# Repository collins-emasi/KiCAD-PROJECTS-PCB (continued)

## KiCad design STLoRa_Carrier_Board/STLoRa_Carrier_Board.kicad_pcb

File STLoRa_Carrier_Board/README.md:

# STLoRa Carrier Board
This is a carrier board for the M.2 Key B System on Module board I designed.

Some of the features include
- SWD Debugging
- UART, I2C peripherals
- Battery powered
- M.2 Key B connector

# Images

# KiCAD
I am using KiCAD v7.0

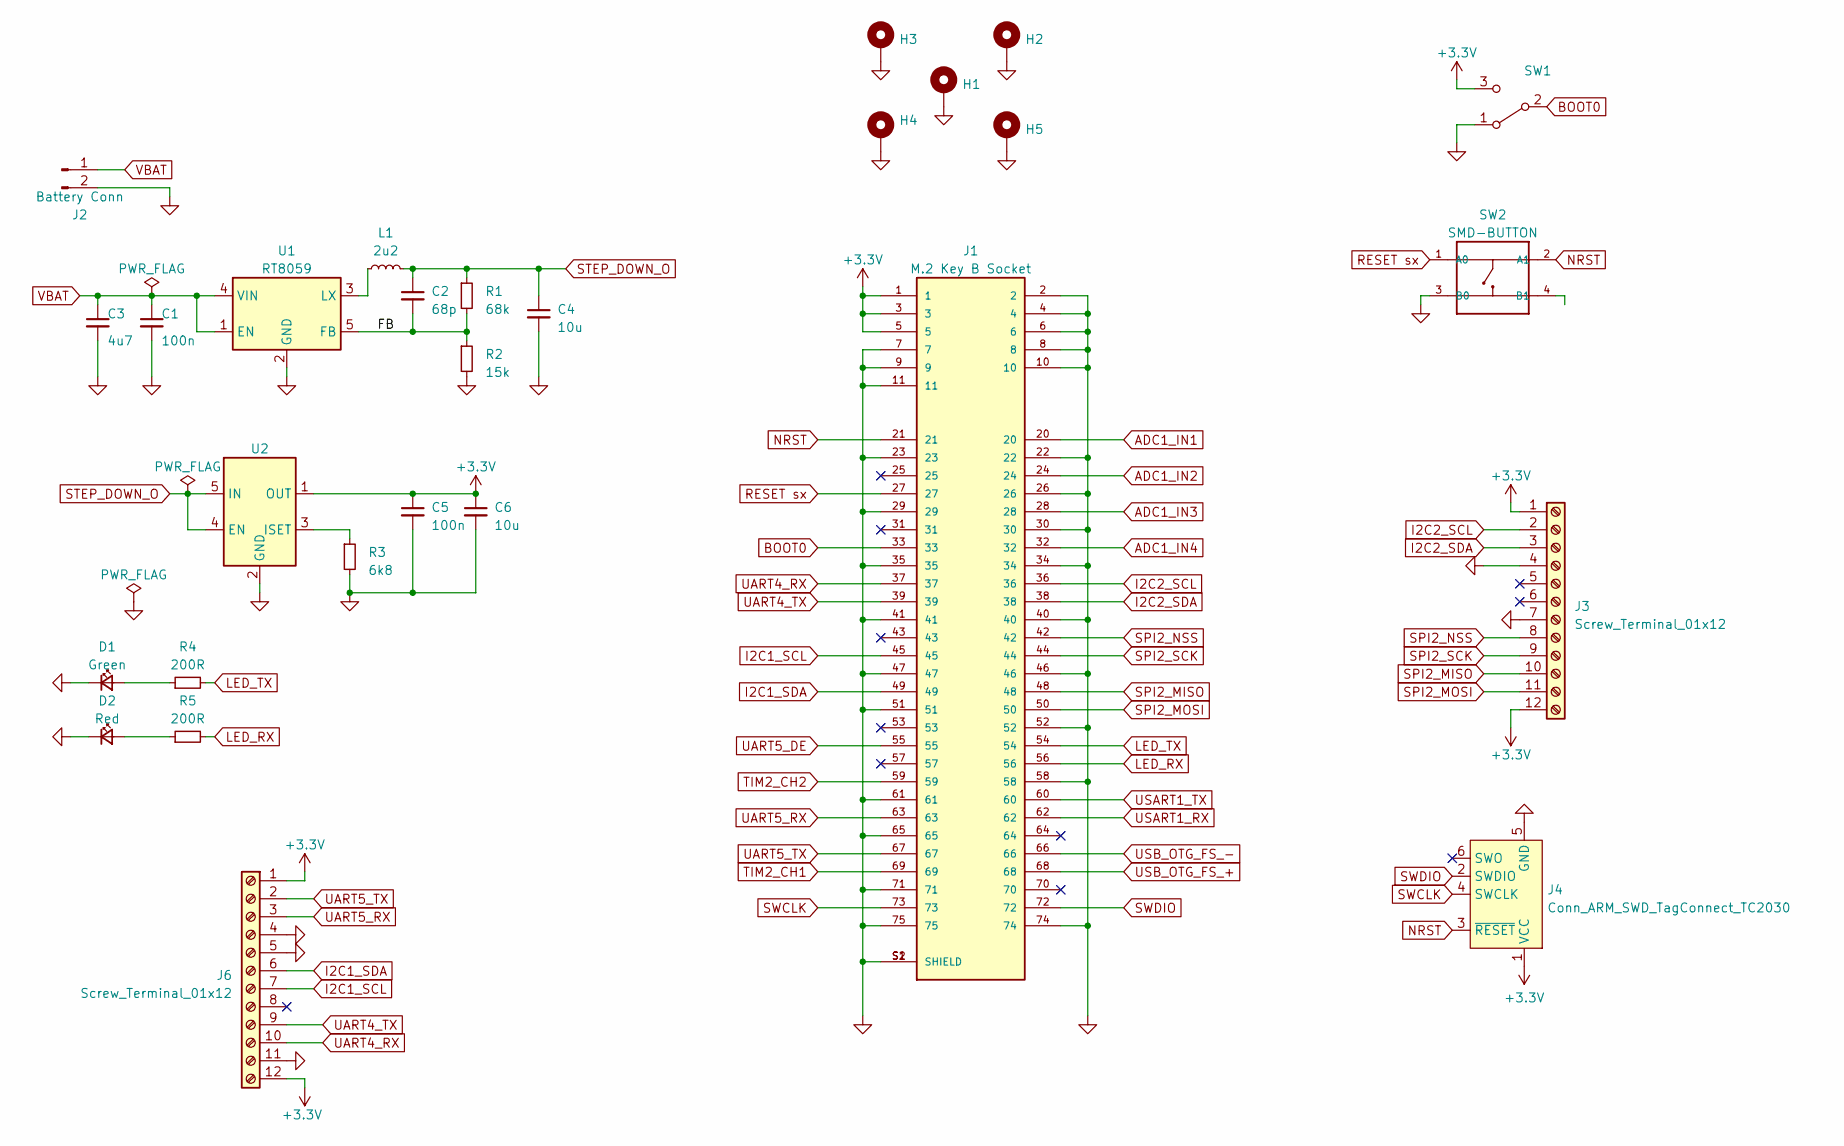
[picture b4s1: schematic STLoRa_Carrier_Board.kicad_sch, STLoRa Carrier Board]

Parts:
C1: 100n; C_1206_3216Metric
C2: 68p; C_1206_3216Metric
C3: 4u7; C_1206_3216Metric
C4: 10u; C_1206_3216Metric
C5: 100n; C_0805_2012Metric
C6: 10u; C_0805_2012Metric
D1: Green; LED_0402_1005Metric
D2: Red; LED_0402_1005Metric
H1: MountingHole_Pad; MountingHole_2.5mm_Pad_Via
H2, H3, H4, H5: MountingHole_Pad; MountingHole_2.5mm_Pad
J1: M.2 Key B Socket
J2: Battery Conn; JST_PH_B2B-PH-K_1x02_P2.00mm_Vertical
J3, J6: Screw_Terminal_01x12; TerminalBlock_Phoenix_MPT-0,5-12-2.54_1x12_P2.54mm_Horizont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
J4: Conn_ARM_SWD_TagConnect_TC2030; Tag-Connect_TC2030-IDC-FP_2x03_P1.27mm_Vertical
L1: 2u2; L_Sunlord_MWSA0503S
R1: 68k; R_0603_1608Metric
R2: 15k; R_0603_1608Metric
R3: 6k8; R_0603_1608Metric
R4, R5: 200R; R_0201_0603Metric
SW1: SW_SPDT; SW_SPDT_PCM12
SW2: SMD-BUTTON; SW4-SMD-5.2X5.2X1.5MM
U1: RT8059; SOT-23-5
U2: SOT-23-5

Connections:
+3.3V: C5.1, C6.1, J1.1, J1.3, J1.5, J3.1, J3.12, J4.1 (VCC), J6.1, J6.12, SW1.3 (C), U2.1 (OUT)
/FB: C2.2, R1.2, R2.1, U1.5 (FB)
ADC1_IN1: J1.20
ADC1_IN2: J1.24
ADC1_IN3: J1.28
ADC1_IN4: J1.32
BOOT0: J1.33, SW1.2 (B)
GND: C1.2, C3.2, C4.2, C5.2, C6.2, D1.1 (K), D2.1 (K), H1.1, H2.1, H3.1, H4.1, H5.1, J1.2, J1.4, J1.6, J1.7, J1.8, J1.9, J1.10, J1.11, J1.22, J1.23, J1.26, J1.29, J1.30, J1.34, J1.35, J1.40, J1.41, J1.46, J1.47, J1.51, J1.52, J1.58, J1.61, J1.65, J1.71, J1.74, J1.75, J1.S1 (SHIELD), J1.S2 (SHIELD), J2.2, J3.4, J3.7, J4.5 (GND), J6.4, J6.5, J6.11, R2.2, R3.2, SW1.1 (A), SW2.3 (B0), U1.2 (GND), U2.2 (GND)
I2C1_SCL: J1.45, J6.7
I2C1_SDA: J1.49, J6.6
I2C2_SCL: J1.36, J3.2
I2C2_SDA: J1.38, J3.3
LED_RX: J1.56, R5.2
LED_TX: J1.54, R4.2
NRST: J1.21, J4.3 (~RESET), SW2.2 (A1)
unnamed: D1.2 (A), R4.1
unnamed: D2.2 (A), R5.1
unnamed: L1.1, U1.3 (LX)
unnamed: R3.1, U2.3 (ISET)
RESET sx: J1.27, SW2.1 (A0)
SPI2_MISO: J1.48, J3.10
SPI2_MOSI: J1.50, J3.11
SPI2_NSS: J1.42, J3.8
SPI2_SCK: J1.44, J3.9
STEP_DOWN_O: C2.1, C4.1, L1.2, R1.1, U2.4 (EN), U2.5 (IN)
SWCLK: J1.73, J4.4 (SWCLK)
SWDIO: J1.72, J4.2 (SWDIO)
TIM2_CH1: J1.69
TIM2_CH2: J1.59
UART4_RX: J1.37, J6.10
UART4_TX: J1.39, J6.9
UART5_DE: J1.55
UART5_RX: J1.63, J6.3
UART5_TX: J1.67, J6.2
USART1_RX: J1.62
USART1_TX: J1.60
USB_OTG_FS_+: J1.68
USB_OTG_FS_-: J1.66
VBAT: C1.1, C3.1, J2.1, U1.1 (EN), U1.4 (VIN)

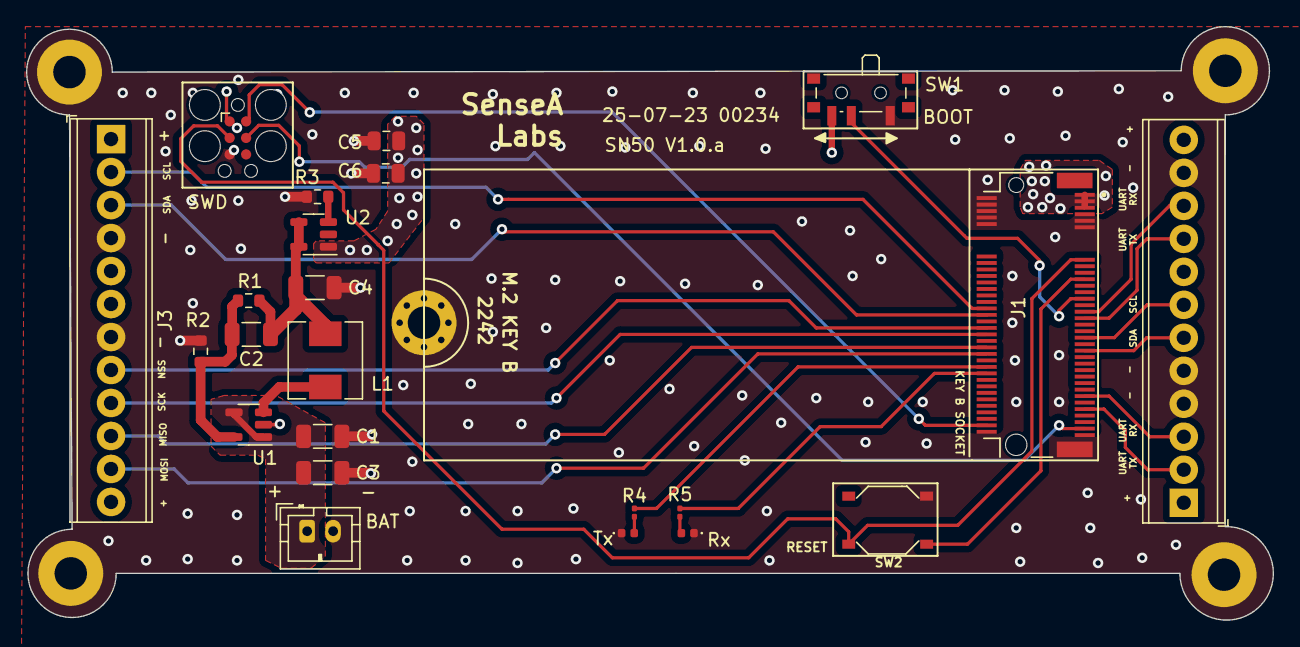
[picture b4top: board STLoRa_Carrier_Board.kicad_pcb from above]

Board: 4 copper layers, 96.0 x 45.7 mm, 28 parts (0 on the bottom side), 28 nets.

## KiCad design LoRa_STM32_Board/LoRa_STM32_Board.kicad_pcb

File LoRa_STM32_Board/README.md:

# KiCAD-PROJECTS-PCB
In this repository, I will be sharing some of the project I'm working on with KiCAD software.

# KiCAD
I am using KiCAD v6.0

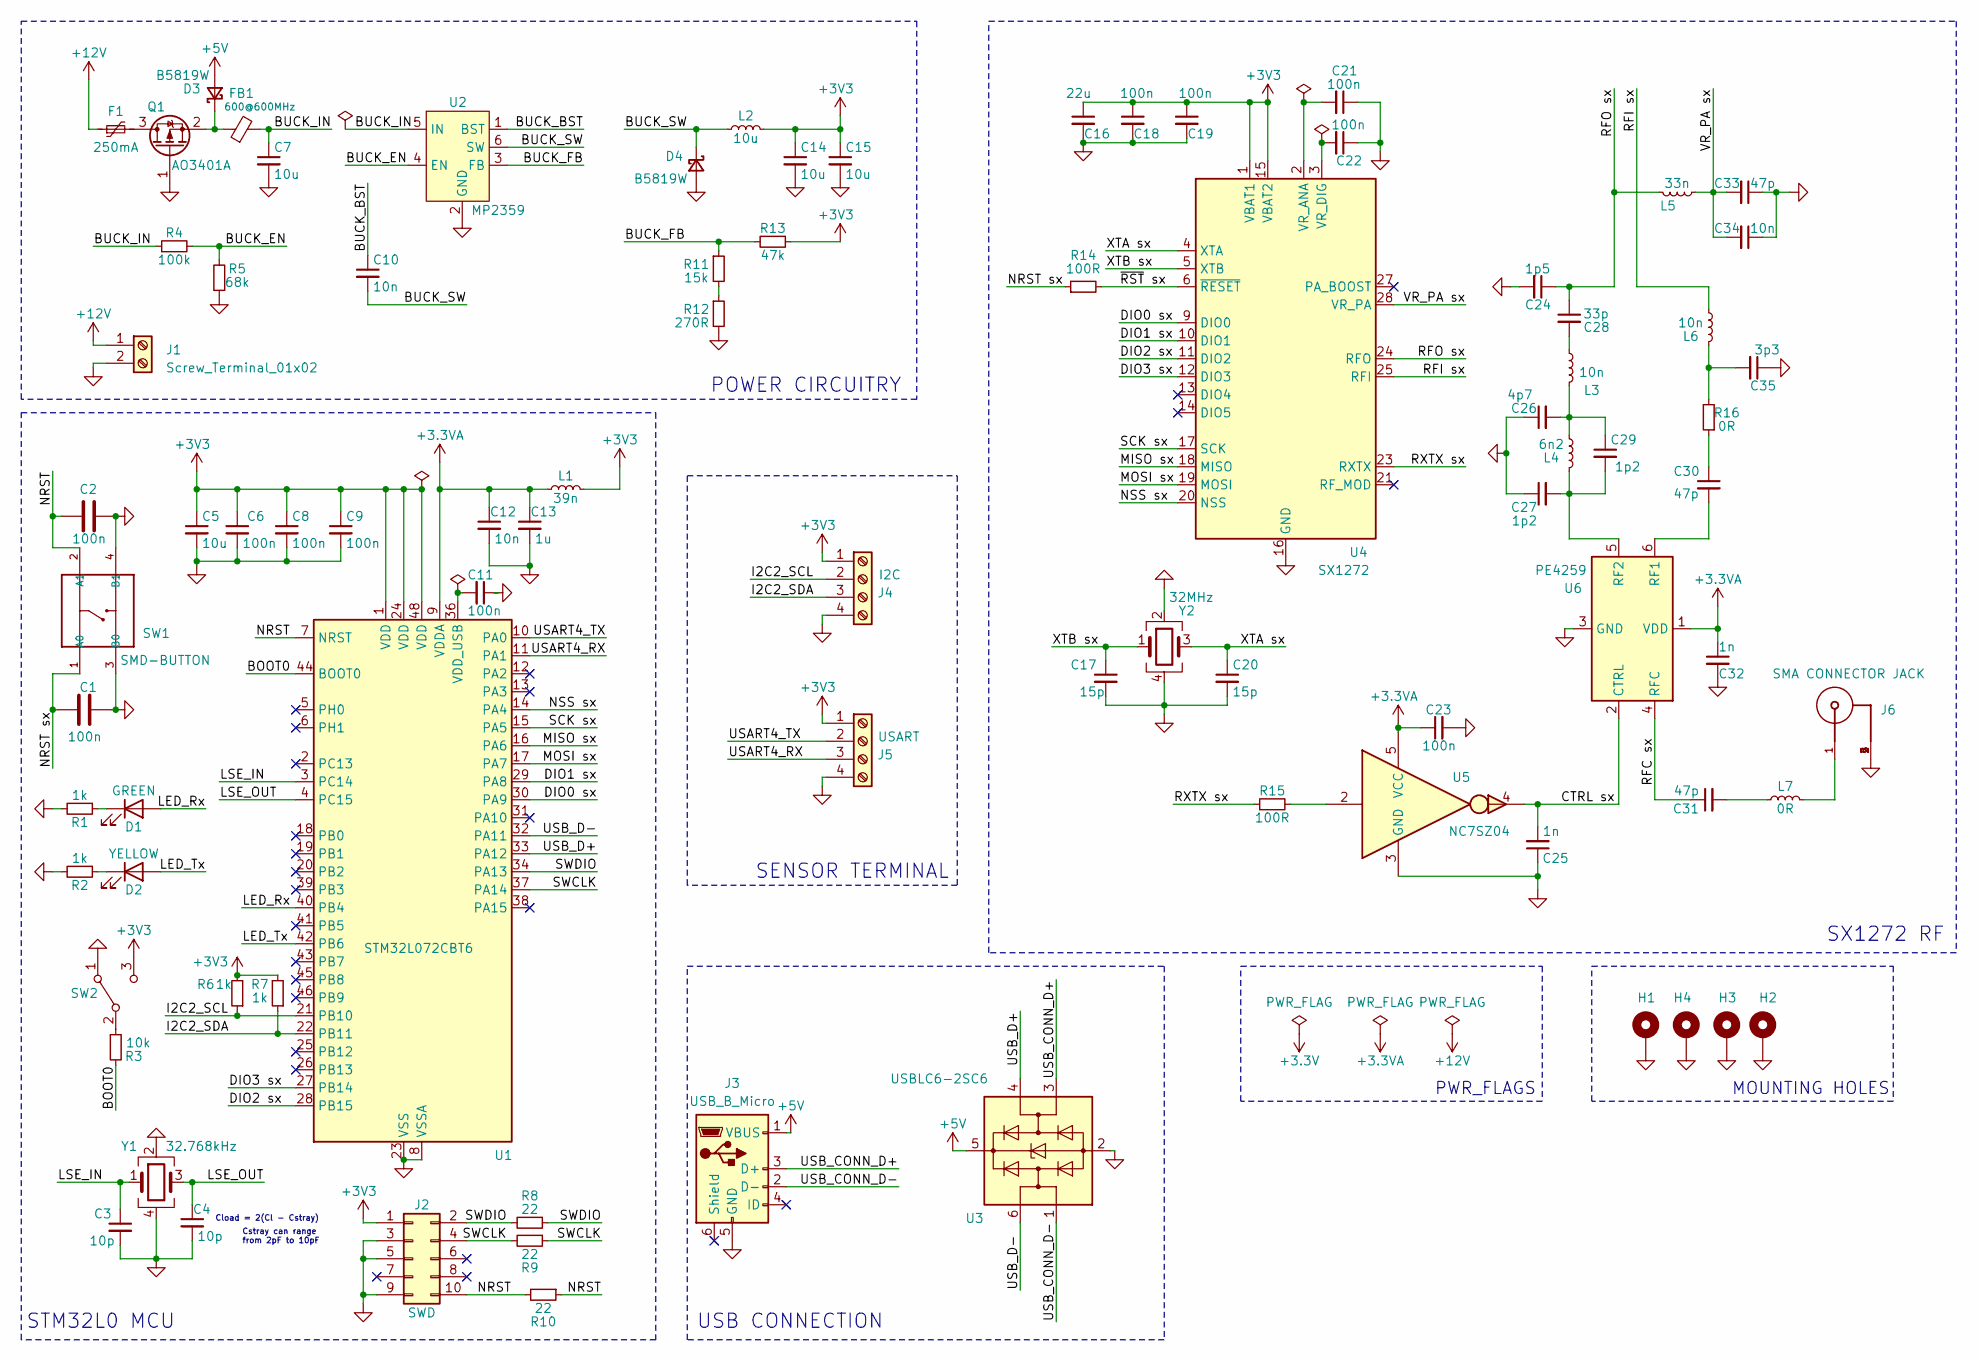
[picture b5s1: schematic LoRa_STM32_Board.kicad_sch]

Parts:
C1, C2, C6, C8, C9, C11, C18, C19, C21, C22, C23: 100n; C_0402_1005Metric
C3, C4: 10p; C_0402_1005Metric
C5: 10u; C_0805_2012Metric
C7: 10u; C_1206_3216Metric
C10: 10n; C_1206_3216Metric
C12, C34: 10n; C_0402_1005Metric
C13: 1u; C_0402_1005Metric
C14, C15: 10u; C_0402_1005Metric
C16: 22u; C_0805_2012Metric
C17, C20: 15p; C_0402_1005Metric
C24: 1p5; C_0402_1005Metric
C25, C32: 1n; C_0402_1005Metric
C26: 4p7; C_0402_1005Metric
C27, C29: 1p2; C_0402_1005Metric
C28: 33p; C_0402_1005Metric
C30, C31, C33: 47p; C_0402_1005Metric
C35: 3p3; C_0402_1005Metric
D1: GREEN; LED_0402_1005Metric
D2: YELLOW; LED_0402_1005Metric
D3, D4: B5819W; D_SOD-123
F1: 250mA; Fuse_1206_3216Metric
FB1: 600@600MHz; L_0805_2012Metric
H1, H2, H3, H4: MountingHole_Pad; MountingHole_3.2mm_M3_Pad_Via
J1: Screw_Terminal_01x02; TerminalBlock_Phoenix_PT-1,5-2-3.5-H_1x02_P3.50mm_Horizontal
J2: SWD; PinHeader_2x05_P1.27mm_Vertical
J3: USB_B_Micro
J4: I2C; TerminalBlock_Phoenix_MPT-0,5-4-2.54_1x04_P2.54mm_Horizontal
J5: USART; TerminalBlock_Phoenix_MPT-0,5-4-2.54_1x04_P2.54mm_Horizontal
J6: SMA CONNECTOR JACK; PART-NUMBER 60311002114501
L1: 39n; L_0402_1005Metric
L2: 10u; L_Sunlord_MWSA0518S
L3, L6: 10n; L_0402_1005Metric
L4: 6n2; L_0402_1005Metric
L5: 33n; L_0402_1005Metric
L7: 0R; L_0402_1005Metric
Q1: AO3401A; SOT-23
R1, R2, R6, R7: 1k; R_0402_1005Metric
R3: 10k; R_0402_1005Metric
R4: 100k; R_0603_1608Metric
R5: 68k; R_0603_1608Metric
R8, R9, R10: 22; R_0402_1005Metric
R11: 15k; R_0603_1608Metric
R12: 270R; R_0603_1608Metric
R13: 47k; R_0603_1608Metric
R14, R15: 100R; R_0402_1005Metric
R16: 0R; R_0603_1608Metric
SW1: SMD-BUTTON; SW4-SMD-5.2X5.2X1.5MM
SW2: SW_SPDT; SW_SPDT_PCM12
U1: STM32L072CBT6; LQFP-48_7x7mm_P0.5mm
U2: MP2359; SOT-23-6
U3: USBLC6-2SC6; SOT-23-6
U4: SX1272; QFN-28-1EP_6x6mm_P0.65mm_EP4.8x4.8mm
U5: NC7SZ04; SOT-353_SC-70-5
U6: PE4259; DFN-6-1EP_2x2mm_P0.65mm_EP1x1.6mm
Y1: 32.768kHz; Crystal_SMD_0603-4Pin_6.0x3.5mm
Y2: 32MHz; Crystal_SMD_2016-4Pin_2.0x1.6mm

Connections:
+3.3VA: C12.1, C13.1, C23.1, C32.1, L1.1, U1.9 (VDDA), U5.5 (VCC), U6.1 (VDD)
+3V3: C5.1, C6.1, C8.1, C9.1, C14.1, C15.1, C16.1, C18.1, C19.1, J2.1, J4.1, J5.1, L1.2, L2.2, R6.2, R7.2, R13.1, SW2.3 (C), U1.1 (VDD), U1.24 (VDD), U1.48 (VDD), U4.1 (VBAT1), U4.15 (VBAT2)
+5V: D3.2 (A), J3.1 (VBUS), U3.5 (VBUS)
+12V: F1.1, J1.1
/BOOT0: R3.2, U1.44 (BOOT0)
/BUCK_BST: C10.1, U2.1 (BST)
/BUCK_EN: R4.2, R5.2, U2.4 (EN)
/BUCK_FB: R11.1, R13.2, U2.3 (FB)
/BUCK_IN: C7.1, FB1.2, R4.1, U2.5 (IN)
/BUCK_SW: C10.2, D4.1 (K), L2.1, U2.6 (SW)
/CTRL sx: C25.2, U5.4, U6.2 (CTRL)
/DIO0 sx: U1.30 (PA9), U4.9 (DIO0)
/DIO1 sx: U1.29 (PA8), U4.10 (DIO1)
/DIO2 sx: U1.28 (PB15), U4.11 (DIO2)
/DIO3 sx: U1.27 (PB14), U4.12 (DIO3)
/I2C2_SCL: J4.2, R6.1, U1.21 (PB10)
/I2C2_SDA: J4.3, R7.1, U1.22 (PB11)
/LED_Rx: D1.2 (A), U1.40 (PB4)
/LED_Tx: D2.2 (A), U1.42 (PB6)
/LSE_IN: C3.1, U1.3 (PC14), Y1.1
/LSE_OUT: C4.1, U1.4 (PC15), Y1.3
/MISO sx: U1.16 (PA6), U4.18 (MISO)
/MOSI sx: U1.17 (PA7), U4.19 (MOSI)
/NRST: C2.1, J2.10, R10.1, R10.2, SW1.2 (A1), U1.7 (NRST)
/NRST sx: C1.1, R14.1, SW1.1 (A0)
/NSS sx: U1.14 (PA4), U4.20 (NSS)
/RFC sx: C31.1, U6.4 (RFC)
/RFI sx: L6.1, U4.25 (RFI)
/RFO sx: C24.1, C28.1, L5.2, U4.24 (RFO)
/RXTX sx: R15.1, U4.23 (RXTX)
/SCK sx: U1.15 (PA5), U4.17 (SCK)
/SWCLK: J2.4, R9.1, R9.2, U1.37 (PA14)
/SWDIO: J2.2, R8.1, R8.2, U1.34 (PA13)
/USART4_RX: J5.3, U1.11 (PA1)
/USART4_TX: J5.2, U1.10 (PA0)
/USB_CONN_D+: J3.3 (D+), U3.3 (I/O2)
/USB_CONN_D-: J3.2 (D-), U3.1 (I/O1)
/USB_D+: U1.33 (PA12), U3.4 (I/O2)
/USB_D-: U1.32 (PA11), U3.6 (I/O1)
/VR_PA sx: C33.2, C34.2, L5.1, U4.28 (VR_PA)
/XTA sx: C20.1, U4.4 (XTA), Y2.3
/XTB sx: C17.1, U4.5 (XTB), Y2.1
/~RST sx: R14.2, U4.6 (~RESET)
GND: C1.2, C2.2, C3.2, C4.2, C5.2, C6.2, C7.2, C8.2, C9.2, C11.1, C12.2, C13.2, C14.2, C15.2, C16.2, C17.2, C18.2, C19.2, C20.2, C21.1, C22.1, C23.2, C24.2, C25.1, C26.1, C27.1, C32.2, C33.1, C34.1, C35.1, D4.2 (A), H1.1, H2.1, H3.1, H4.1, J1.2, J2.3, J2.5, J2.9, J3.5 (GND), J4.4, J5.4, J6.2, J6.3, J6.4, J6.5, Q1.1 (G), R1.2, R2.2, R5.1, R12.2, SW1.3 (B0), SW1.4 (B1), SW2.1 (A), U1.8 (VSSA), U1.23 (VSS), U1.35 (VSS), U1.47 (VSS), U2.2 (GND), U3.2 (GND), U4.16 (GND), U4.22 (GND), U4.26 (GND), U4.29 (GND), U5.3 (GND), U6.3 (GND), Y1.2, Y1.4, Y2.2, Y2.4
unnamed: C11.2, U1.36 (VDD_USB)
unnamed: C21.2, U4.2 (VR_ANA)
unnamed: C22.2, U4.3 (VR_DIG)
unnamed: C26.2, C29.1, L3.2, L4.1
unnamed: C28.2, L3.1
unnamed: C30.1, R16.1
unnamed: C31.2, L7.1
unnamed: C35.2, L6.2, R16.2
unnamed: D1.1 (K), R1.1
unnamed: D2.1 (K), R2.1
unnamed: D3.1 (K), FB1.1, Q1.2 (S)
unnamed: J6.1, L7.2
unnamed: F1.2, Q1.3 (D)
unnamed: R11.2, R12.1
unnamed: R15.2, U5.2
unnamed: R3.1, SW2.2 (B)
unnamed: C30.2, U6.6 (RF1)
unnamed: C27.2, C29.2, L4.2, U6.5 (RF2)

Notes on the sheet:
MOUNTING HOLES
SX1272 RF
PWR_FLAGS
Cload = 2(Cl - Cstray)
SENSOR TERMINAL
USB CONNECTION
POWER CIRCUITRY
STM32L0 MCU
Cstray can range from 2pF to 10pF

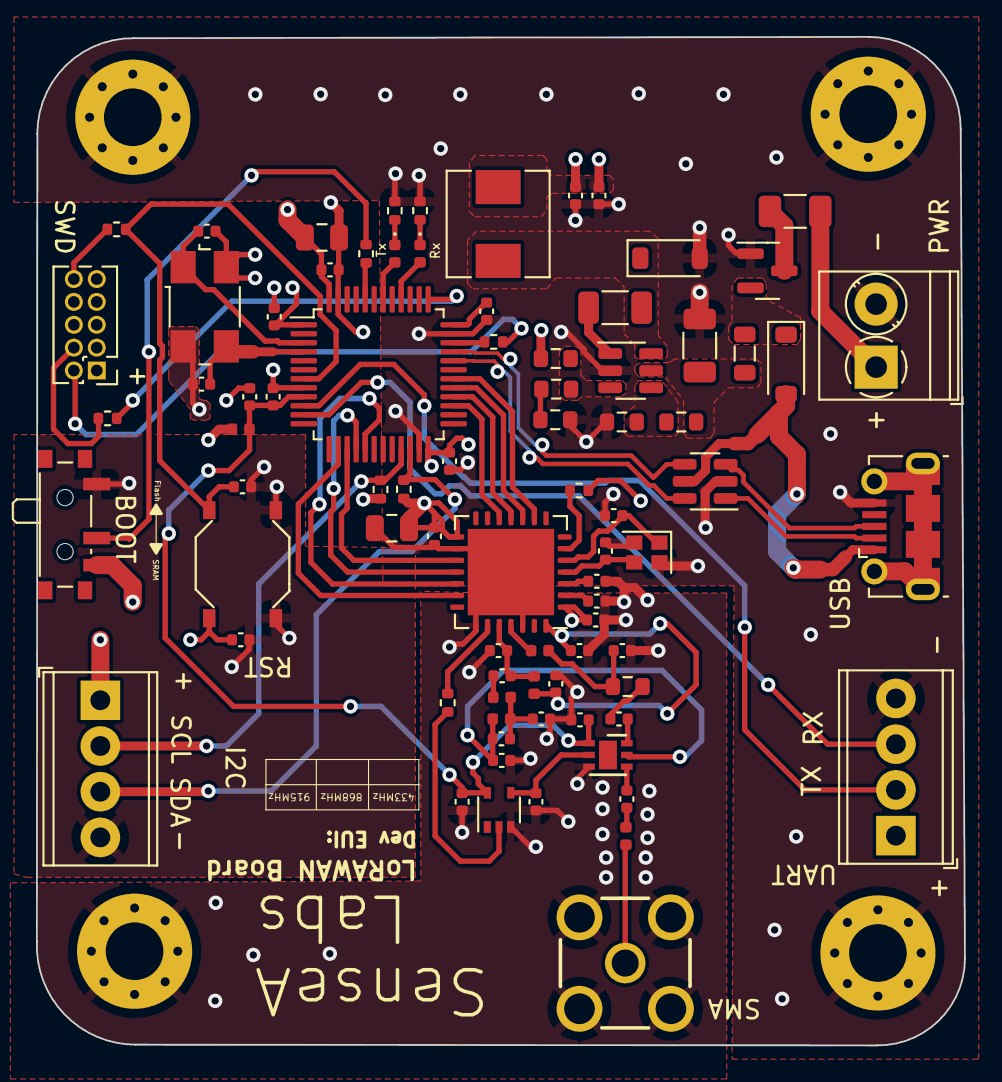
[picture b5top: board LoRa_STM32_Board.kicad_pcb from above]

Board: 4 copper layers, 51.6 x 56.0 mm, 85 parts (0 on the bottom side), 62 nets.

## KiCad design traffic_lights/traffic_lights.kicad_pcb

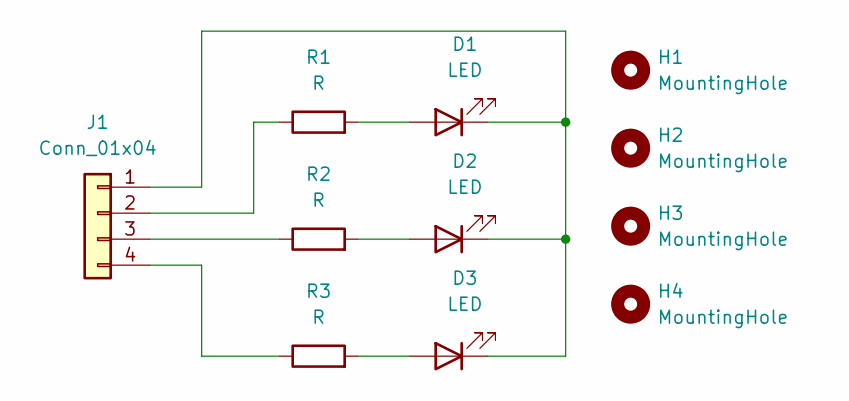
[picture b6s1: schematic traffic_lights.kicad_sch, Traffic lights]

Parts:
D1, D2, D3: LED; LED_D3.0mm
H1, H2, H3, H4: MountingHole; MountingHole_2.5mm_Pad
J1: Conn_01x04; PinHeader_1x04_P2.54mm_Horizontal
R1, R2, R3: R; R_Axial_DIN0204_L3.6mm_D1.6mm_P5.08mm_Horizontal

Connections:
unnamed: D1.1 (K), D2.1 (K), D3.1 (K), J1.1
unnamed: D1.2 (A), R1.2
unnamed: D2.2 (A), R2.2
unnamed: D3.2 (A), R3.2
unnamed: J1.2, R1.1
unnamed: J1.3, R2.1
unnamed: J1.4, R3.1

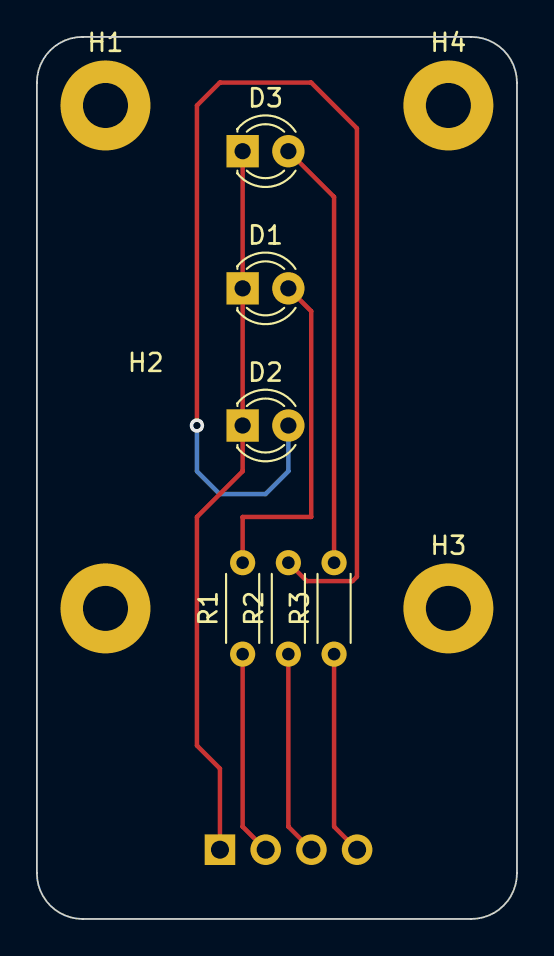
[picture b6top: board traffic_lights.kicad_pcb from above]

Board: 2 copper layers, 26.7 x 49.0 mm, 11 parts (1 on the bottom side), 7 nets.

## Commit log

2022-04-25 Added the traffic lights project
2022-04-25 Changed the readme.md file
2023-09-12 Added Readme to projects
